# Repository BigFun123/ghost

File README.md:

# Ghost Controller

## ESP32-S3

The default PlatformIO environment is `esp32-s3-devkitc-1`, targeting the
ESP32-S3-DevKitC-1 with an ESP32-S3-WROOM-1 N16R8 module: 16 MB quad-SPI flash
and 8 MB octal PSRAM. The base PlatformIO board name may still display N8;
the project overrides its flash size and memory mode for N16R8. PSRAM is enabled
with `qio_opi` and `BOARD_HAS_PSRAM`; it does not increase persistent storage.

`partitions_esp32s3_16mb.csv` reserves two 2 MiB firmware slots for OTA updates
and 12,517,376 bytes (11.9375 MiB / 12.52 MB) for LittleFS. The partition named
`spiffs` uses the ESP32 Arduino filesystem partition convention; its contents
are LittleFS, selected by `board_build.filesystem`.

The external PCA9685 uses **SDA GPIO4 and SCL GPIO5** on both targets. Connect
to those GPIO numbers on the S3, with a shared ground and 3.3 V I2C pull-ups.
The onboard OLED remains disabled. The existing servo configuration is retained.

`BoardRgbLed` controls the onboard addressable LED and starts it blue at a
brightness of 64/255. It provides `setColor(red, green, blue)` and `off()`.
The default follows the Arduino board's `PIN_RGB_LED` (GPIO48). For a DevKitC-1
v1.1 with its LED on GPIO38, add `-DCONTROLLER_RGB_LED_PIN=38` to the S3
environment's `build_flags`. On ESP8266 the class does nothing.

Build firmware and filesystem:

```powershell
pio run -e esp32-s3-devkitc-1
pio run -e esp32-s3-devkitc-1 -t buildfs
```

The first installation on the S3 requires USB, including the new partition table
and filesystem. Back up config and sequences from the old controller first;
the LittleFS images and firmware for the two chips are not interchangeable.
When ready to install, connect the S3 and use:

```powershell
pio run -e esp32-s3-devkitc-1 -t upload
pio run -e esp32-s3-devkitc-1 -t uploadfs
```

The existing native USB CDC flags are retained. Use the USB port appropriate to
your board; an explicit `--upload-port COMx` can select it when needed.

Passing an IP address to `--upload-port` automatically selects OTA, even with
the base environment. For the initial installation use a serial port, for example:

```powershell
pio run -e esp32-s3-devkitc-1 -t upload --upload-port COM10
pio run -e esp32-s3-devkitc-1 -t uploadfs --upload-port COM10
```

Replace COM10 with the board's actual port (`pio device list`). If the uploader
cannot connect, hold BOOT, press and release RESET, then release BOOT and retry.

Subsequent updates can use `esp32-s3-devkitc-1_ota` at
`ghost-controller.local`, with `OTA_PASSWORD` set for the uploader. Wi-Fi and
device OTA credentials are supplied through the existing private
`include/WifiCredentials.h`. `upload_html.ps1` now defaults to the S3 OTA
filesystem target. A filesystem upload replaces saved files with `data/`.

For an OTA firmware update to a specific IP, use the OTA environment so its
authentication flags are included:

```powershell
pio run -e esp32-s3-devkitc-1_ota -t upload --upload-port 192.168.3.36
```

`No response from the ESP` means no OTA invitation response arrived. Confirm
the S3 is already running this firmware, its current IP is correct, and its
serial log reports `OTA ready`. This firmware disables OTA when its configured
OTA password is empty. For an already initialized device, also check local
firewall/network access to UDP 3232 and the uploader's return TCP connection.

The original `nodemcuv2` and `nodemcuv2_ota` environments remain available for
the ESP8266. Use `./upload_html.ps1 -Environment nodemcuv2_ota` for its filesystem.

## Robot folders

The mixer motion button cycles through immediate (`-`), smooth (`S`, with
acceleration/deceleration), and linear (`/`, constant angular command speed).
Low/medium/high speeds apply to manual timed moves. In a sequence, linear moves
use the step duration regardless of distance or selected speed, including the
first step. A 10° to 90° linear move in a 2000 ms step takes 2000 ms at 1× playback;
at 2× it takes 1000 ms. Smooth step moves retain their selected speed.
Sequence steps save the mode; older immediate/smooth steps retain their meaning.
The servo settings initial motion mode also accepts `linear`.
Step playback sends one servo batch to the controller. Offline playback sets
every target with a shared start time before rendering, so one servo cannot
delay another while the canvas is redrawn. This requires matching firmware
and frontend versions.
Color steps can be selected to apply their RGB value immediately without moving
servos. The ESP32 model shows the current RGB color with a glowing LED; live
status refreshes report the controller's current color. Black switches the glow off.

The **Robot** entry is a physical ESP32-style board in the 3D hierarchy. Select it
to edit robot name/folder settings and its position/rotation. Drag components
onto the board to attach them, or onto **Scene** to detach them. New components
attach to Robot by default. Legacy configs gain a board at the origin when
opened; existing root components attach to it, with their poses preserved.
Use Save robot to persist the added board. It consumes no servo output channel.

Each robot is stored in `data/robots/<robot name>/` with `config.json` and
`sequence_a.json` through `sequence_j.json`. Missing slots start empty. The
folder name is the robot name; `data/robots.json` records the available folders
and the selected robot. The same layout is used in the controller's LittleFS.
Saved live servo positions are also kept inside that robot's folder.

In Setup, use **New robot**, enter its **Robot name**, then **Save robot** to
create the folder. Choose an existing **Robot folder** and click **Load robot**
to load its configuration and sequence slots. Edit **Robot name** and click
**Save robot** to rename its folder; its config and sequences move together.
Existing folder names cannot be overwritten. **Import config** imports an older
standalone JSON config into a new robot; Save robot creates its named folder.
Changing an existing folder's topology still requires reviewing its sequences.

The local server migrates legacy root-level config and compatible sequence files
to the `Robot` folder on first use, retaining the originals as backups. Sequences
whose servo count does not match remain only in the legacy backup location.
The included `Walker` folder contains the imported walker config and an empty A slot.

Selecting a different robot on the controller turns off the current PWM outputs
and blocks servo commands until restart. Editing and sequences use offline
simulation until then. Click **Reboot** after saving to apply the selected robot
to hardware. These changes require both firmware and filesystem uploads;
building them locally does not update the controller.

## Hardware components

### Adding a 3D component

Each file in `data/components/` owns its drawing and registers with
`componentRegistry` from `registry.js`. The same draw function supplies visible
geometry, physics shapes and sensor-hit surfaces. Optional `drawOverlay` owns
effects such as the ESP32 LED glow and the VL53L0X beam.

To add a passive component, create its file with a draw function and registration:

```javascript
function drawExample({ box, label }) {
  box([0, 0, 0], [20, 2, 40], "#aebbc5", false);
  label([0, 8, 0]);
}
componentRegistry.register({
  objectType: "Example panel",
  order: 110,
  defaults: {},
  draw: drawExample
});
```

Add its script to `data/index.html` after `registry.js` and before `app.js`.
The picker, loaded-config validation, drawing and physics discover it through
the registry; no `app.js` changes are needed. Servo variants additionally register
`model`, `choice`, `label` and their model/type `defaults`; Robot is non-selectable
because the robot root is created automatically. Draw contexts include `node`,
`purpose` (`render`/`physics`) and shared `state` where applicable.

Restart the local server to regenerate `data/components/catalog.json`, or run
`node devserver/component-registry.js` before a filesystem build. Firmware uses
that catalog for type/model validation and serves model scripts generically.
Deploy the updated files together; this registry migration also requires the
updated firmware once. Subsequent passive models need only a filesystem update.

Setup also includes aluminium panels sized 50×50×2 mm and 50×100×2 mm,
a solid 50 mm box, and a stylized slotted 20×20×100 mm aluminium extrusion.
Panels lie in local X/Z; the extrusion runs along local Y. They attach like other
components, participate in physics and simulated sensor ray hits, and consume
no servo outputs. Dimensions are illustrative rather than manufacturing models.

## Distance sensor component

In Setup, select **VL53L0X V2 Time of Flight Sensor** under Add component,
then position, rotate and parent it before saving the configuration. The
preview uses a stylized board with its sensing direction along local +Z.
It participates in preview physics as a fixed attachment and uses no servo channel.

The 3D view draws a dotted beam along the sensor's local +Z direction and labels
the nearest simulated surface distance in millimetres. The floor at world Y=0 is
solid, including when physics is disabled or the grid is hidden. The display ray
extends up to 2000 mm; this is a visualization limit, not a hardware specification.
Sensor distance labels remain visible when component name labels are disabled.
The firmware supports one physical VL53L0X at I2C address `0x29` on the
PCA9685 pass-through I2C header. Connect SDA to SDA (controller GPIO4), SCL to
SCL (GPIO5), and GND to the common ground. Use a supply supported by your
breakout and keep SDA/SCL pull-ups at 3.3 V; the PCA9685 servo V+ rail is not
the sensor supply. The header shares the controller bus, so no additional
GPIO or PCA9685 servo channel is needed. Multiple sensors at the default
address require separate XSHUT wiring/address assignment, which is not supported.

Firmware starts continuous ranging at 100 ms intervals, polls completed results
without waiting for a measurement, and retries unavailable sensors every five
seconds. `GET /api/sensors` returns a `vl53l0x` object; `GET /api/status` includes
the same object under `sensors.vl53l0x`. Example:

```json
{"vl53l0x":{"model":"VL53L0X","address":41,"ready":true,"valid":true,"distanceMm":325,"rangeStatus":11,"sampleAgeMs":42}}
```

`ready` indicates initialization, while `valid` indicates a current successful
measurement. `distanceMm` is null for missing, invalid, or stale readings (over
500 ms). `rangeStatus` is the raw device status (11 means range complete), and
`sampleAgeMs` is the age of the latest completed sample; both are null before
any sample. API handlers return cached telemetry and do not initiate I2C reads.
The editor beam and labels still show simulated geometry, not API telemetry.
The driver uses the [Pololu VL53L0X library](https://github.com/pololu/vl53l0x-arduino).
These changes require a firmware upload to take effect on the controller.

For the 30 cm walking task, distance change to a fixed reference surface can estimate
forward displacement while the sensor keeps the same heading. One range
measurement does not determine full position or sideways drift.

## GY-801 component

In Setup, click **+**, choose **Sensors**, select **GY-801**, then click
**Add component**. It supports placement, rotation, parenting, robot saving,
physics geometry and simulated range-sensor hits without using a servo output.

The stylized blue board has a 25.8 x 16.8 mm outline, based on the
[GY-801 module datasheet](https://okystar.com/wp-content/uploads/2017/07/OKY3062-5.pdf).
It represents the gyro, accelerometer, compass and barometer packages; chip layout
and mounting details are illustrative. This adds the scene component only;
hardware sensor drivers and live IMU/pressure telemetry are not implemented.

GY-801 scene output is available in **Metrics**. The **Units** selector switches
between rotation (degrees), gyro (degrees/second), acceleration (metres/second
squared), altitude (metres) and pressure (hPa). All GY-801 traces are marked
**(sim)** and derive from the mounted board's world pose, including parent and
physics motion. Acceleration includes gravity; pressure uses an approximate
standard atmosphere with scene Y=0 as sea level. These are simulated outputs,
including when connected to a controller, rather than live sensor telemetry.
Derivative readings start after sufficient samples and reset after long gaps.

The full simulated GY-801 output includes gyro X/Y/Z (degrees/second),
accelerometer X/Y/Z (m/s²), magnetometer X/Y/Z (microtesla), compass heading
(degrees), barometric pressure (hPa) and temperature (degrees Celsius), plus
scene orientation and altitude. Select **µT** for the compass field axes and
**°C** for temperature. The compass uses a synthetic uniform world field
`[0, -20, 40] µT`, with north along +Z and up along +Y, rather than a local
Earth-field estimate. Heading follows the board's horizontal +Z direction and
is unavailable when that axis is vertical. Temperature follows the simulated
atmosphere's lapse rate; it is not a live chip-temperature measurement.

## Component mass

Every component's Setup parameters include **Physics > Mass (g)**. Enter a
positive total mass in grams and use **Save robot** to persist it. Clear the
input to return to the legacy geometry-density estimate. Mass is stored as
`massGrams` and loaded by both the local editor and controller configuration.

The physics adapter converts grams to kilograms, divides the mass across the
component's collider volumes (including servo body/shaft shapes), and sums
attached component masses into welded bodies. Null components can carry mass
without visible geometry. Changing mass rebuilds the running physics assembly
at its configured pose, as other topology changes do.

## Component power estimates

Every component model in data/components/ registers a getPower() method returning
{ min, max } in watts. Edit that method to set the model's power defaults.
Powered models other than TD-7120 use provisional 0.1-1 W placeholders; passive models
use 0 W. Replace the placeholders with measured or datasheet values.

Each component can override its model defaults with minPowerWatts and
maxPowerWatts in config.json. Edit them in Setup under Estimated power, or in
Servo Settings. A complete nonnegative range overrides the model; blank/null
or incomplete ranges use getPower() defaults. Explicit 0/0 is a valid override.

Servo meters and Power metrics share the same estimates, interpolating between
minimum and maximum using movement activity. Off/muted outputs show zero.
Controller and sensor estimates use their minimum as an idle baseline. The
master meter sums all component estimates, including model defaults.
These are estimates, not live electrical measurements.

Configure electrical ratings in Setup or Servo Settings using powerVoltageVolts,
idleCurrentAmps, runningCurrentAmps and peakCurrentAmps. Watts are calculated as
voltage times current; convert mA to A by dividing by 1000. Editing electrical
inputs clears direct watt overrides. Complete watt overrides still take priority
if entered afterwards. Normal movement interpolates toward running power; peak
power is shown in the tooltip and is not treated as a measured stall.
Meter segments use normal-running power as their full scale.

TD-7120 defaults now use the supplied ratings: idle 0.040 A; no-load running
0.210 A at 4.8 V to 0.260 A at 7.2 V; peak 2.1 A at 4.8 V, 2.7 A at 7.2 V,
and 3.3 A at 8.4 V. Intermediate currents are linearly interpolated estimates.
Its assumed supply is 4.8 V unless overridden; set the actual supply voltage.
The 0.040 A idle value is an upper estimate for the quoted less-than-40 mA figure.

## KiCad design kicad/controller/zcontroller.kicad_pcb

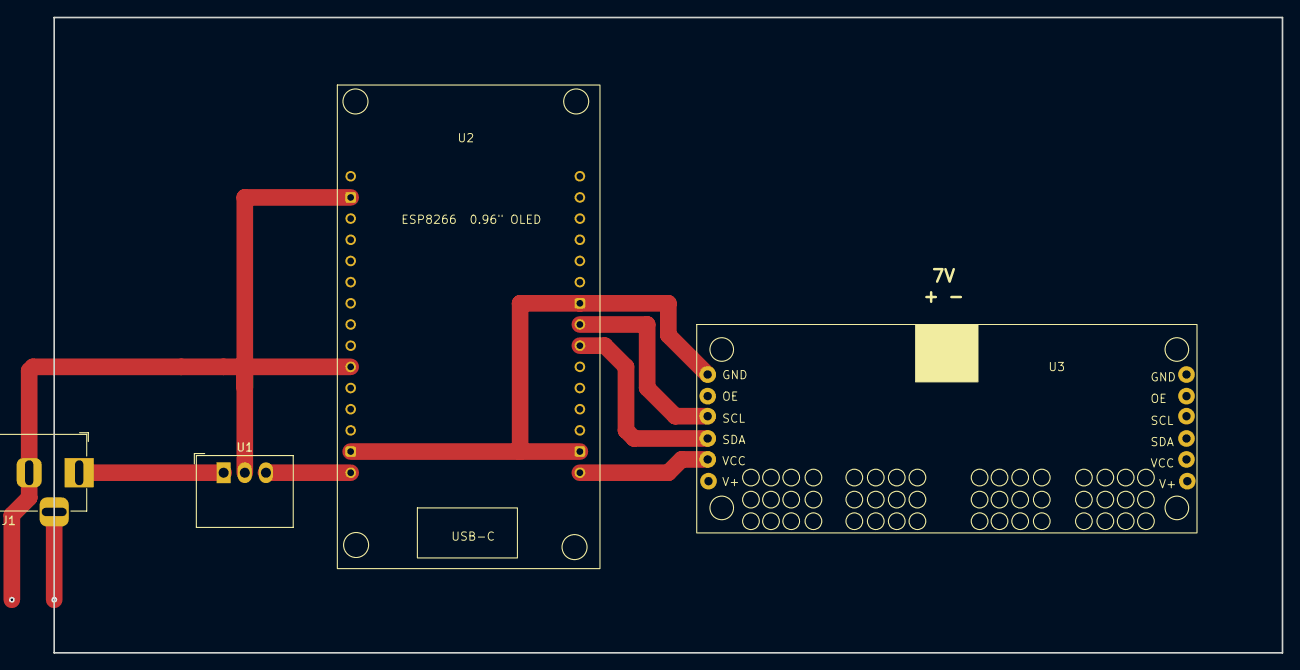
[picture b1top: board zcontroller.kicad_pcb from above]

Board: 2 copper layers, 147.3 x 76.2 mm, 4 parts (0 on the bottom side), 5 nets.

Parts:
J1: Barrel_Jack; BarrelJack_Horizontal
U1: R-78B5.0-2.0; Converter_DCDC_RECOM_R-78B-2.0_THT
U2: ESP8266 with 0.96 inch oled v2.1.2
U3: 16 Channel Servo Controller

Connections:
GND: J1.2, U1.2 (GND), U2.2 (GND), U2.10 (GND), U2.14 (GND), U2.22 (GND), U2.29 (GND), U3.1 (GND)
unnamed: J1.1, U1.1 (IN)
unnamed: U1.3 (OUT), U2.15 (VIN)
unnamed: U2.23 (D5(GPIO14)), U3.3 (SCL)
unnamed: U2.24 (D6(GPIO12)), U3.4 (SDA)
